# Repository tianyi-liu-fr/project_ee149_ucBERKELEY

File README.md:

# EECS149/249 VISION++ Project
Project developed by Enrique Flores Medina and Tianyi Liu, as conceptualized by PhD Prabal Dutta.

Vision++ is a glove designed to empower low vision people, by turning any readable text into speech. By pressing a button, the glove captures an image. If it contains any text, it is automatically turned into speech through a smartphone app. Demonstration video: https://youtu.be/q09WU-yeQec

# Hardware
The hardware folder contains the files used to design a PCB and an enclosure. The ESP32-CAM development board was used, and a PCB and enclosure were designed to adjust to its capabilities.

# Software
The software folder contains the source code for the ESP32-CAM, which allows it to capture and upload images to a cloud server with the press of a button. It also contains two python scripts: one downloads the images uploaded by the ESP32-CAM to the cloud server, and another one extracts the text detected in those images. Finally, the Smartphone App folder contains the file used to develop the app that turns the text into speech. Additionally, there is a Finite State Machine (FSM) diagram showing the behavior of each piece of software.

# Documentation
The documentation folder includes the project proposal and two milestones, showing how the project started, how it progressed, and how it turned out in the end.

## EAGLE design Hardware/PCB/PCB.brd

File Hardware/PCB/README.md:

# What is in the PCB?
The PCB allows for the connection of pin 13 in the ESP32-CAM board to GND through a push button, which serves as the trigger to capture images. It also allows for the use of power supplies from 5VDC up to 35VDC, by using an L7805 5V voltage regulator and two capacitors for noise filtering. Finally, the PCB is equipped with a voltage divisor that is connected to an ADC pin in the board. If a 9VDC battery is used as the power supply, two 10kOhm resistors can be used to measure its voltage level. This last part, however, is not yet implemented in the source code. 

The images show a CAD of the PCB and of the real assembled PCB. The real assembled PCB shown in outdated.

# Libraries
Footprint for the ESP32-CAM development board as ESP32-CAM.lbr, and footprint for the L7805 voltage regulator as L7805.lbr

# Board, Schematic, and Gerbers
Files for the PCB design are shown as PCB.brd, PCB.sch, and Gerbers.zip. The pinout for the ESP32-CAM development board can be found in: https://randomnerdtutorials.com/esp32-cam-ai-thinker-pinout/

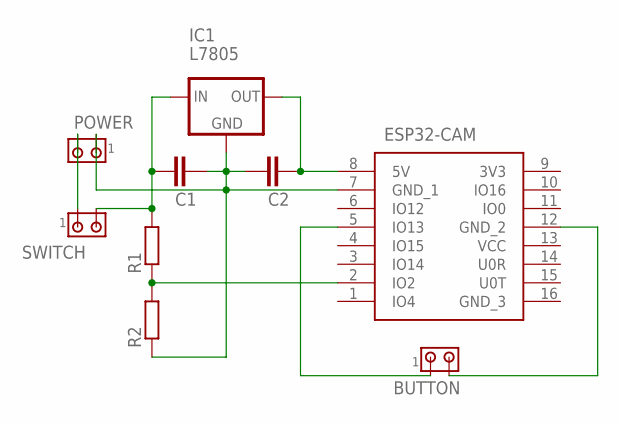
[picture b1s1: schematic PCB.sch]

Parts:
BUTTON: MTA02-156; 1X2MTA
C1, C2: C2,5-3; C2.5-3
IC1: L7805; 78XXS
POWER: MTA02-156; 1X2MTA
R1, R2: R-EU_0207/15; 0207/15
SWITCH: MTA02-156; 1X2MTA
U$1: ESP32-CAM

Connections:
unnamed: BUTTON.2, U$1.12 (GND_2)
unnamed: BUTTON.1, U$1.5 (IO13)
unnamed: POWER.2, SWITCH.1
unnamed: C1.2, C2.1, IC1.GND, POWER.1, R2.1, U$1.7 (GND_1)
unnamed: C2.2, IC1.OUT, U$1.8 (5V)
unnamed: C1.1, IC1.IN, R1.2, SWITCH.2
unnamed: R1.1, R2.2, U$1.2 (IO2)

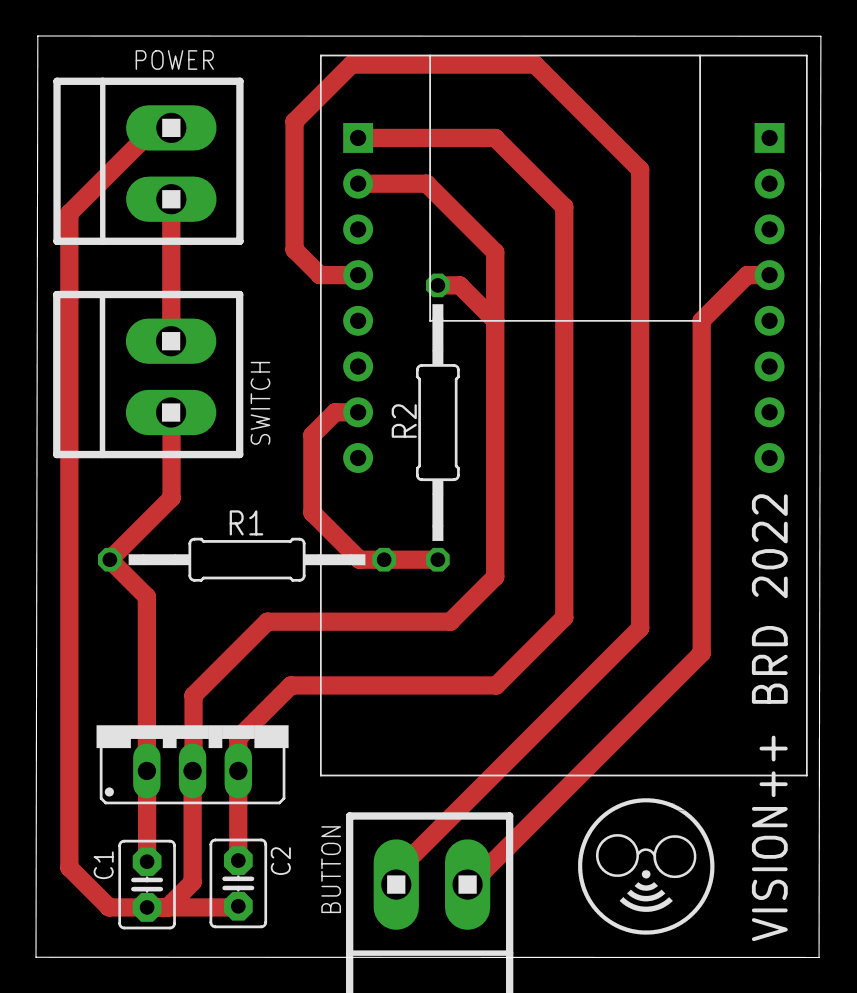
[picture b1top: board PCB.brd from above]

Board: 2 copper layers, 43.6 x 51.2 mm, 9 parts (0 on the bottom side), 7 nets.

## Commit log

2022-10-24 Rename README.md to PROJECT_CHARTER.md
2022-10-24 Rename PROJECT_CHARTER.md to Project_charter.md
2022-11-05 Create h
2022-11-07 Create a
2022-11-07 Create ahah
2022-11-23 Add files via upload
    last version 11/22/2022
2022-12-21 Create a
2022-12-21 Rename project_id_template.json to visonplusplus-ad4a007f31f0.json
